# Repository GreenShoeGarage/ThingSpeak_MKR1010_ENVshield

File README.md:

View this project on [CADLAB.io](https://cadlab.io/project/23807). 

# Workspace Health Monitoring Gadget

[https://greenshoegarage.com/2020/10/learning-from-covid-19/](https://greenshoegarage.com/2020/10/learning-from-covid-19/)

## Goal

An open-source device that can monitor 8+ key environmental factors that affect people's perception of a healthy and productive workspace:

* Temperature
* Pressure
* eCO2
* Humidity
* Brightness
* Noise
* TVOC
* PM 2.5um

### Code and hardware is a prototype, no guarentee of any sort is implied. Use at your own risk.

## Functionality

1. Monitor 8 environmental factors
   1. Central processing of all sensor data
2. Record the telemetry locally
   1. 24-hour rolling log
   2. Store on microSD card
3. Display the telemetry locally
   1. Display new data point every 3 seconds
4. Transmit telemetry to web-based cloud service
   1. Send latest sensor readings every 10 minutes

## Bill of Materials

| Supplier | Product ID | Quantity | Description | Unit Price | Function | 
| :--- | :--- | :--- | :--- | :--- | :--- |  
| Mouser | 782-ABX00023 | 1 | MKR1010 | $32.10 | Processing and Comms | 
| Mouser | 782-ASX00011 | 1 | MKR ENV Shield | $34.40 | Temp, UVA/UVB/UV Index, Humidity, Pressure, Lux |
| Adafruit | 3709 | 1 | SGP30 Air Quality Sensor Breakout | $19.95 | VOC, eCO2 | 
| Adafruit | 4632 | 1 | PMSA003I Air Quality Breakout | $44.95 | Particulate Matter | 
| Adafruit | 421 | 1 | I2S MEMS Microphone Breakout SPH0645LM4H | $6.95 | Noise | 

Get the PCB from OSHPark: [https://oshpark.com/shared\_projects/NU4I8Xzd](https://oshpark.com/shared_projects/NU4I8Xzd)

PartsBox Project BOM: [https://partsbox.com/mbparks/project/1s51nh9teghyx9e4by3gwn3nxp/](https://partsbox.com/mbparks/project/1s51nh9teghyx9e4by3gwn3nxp/)

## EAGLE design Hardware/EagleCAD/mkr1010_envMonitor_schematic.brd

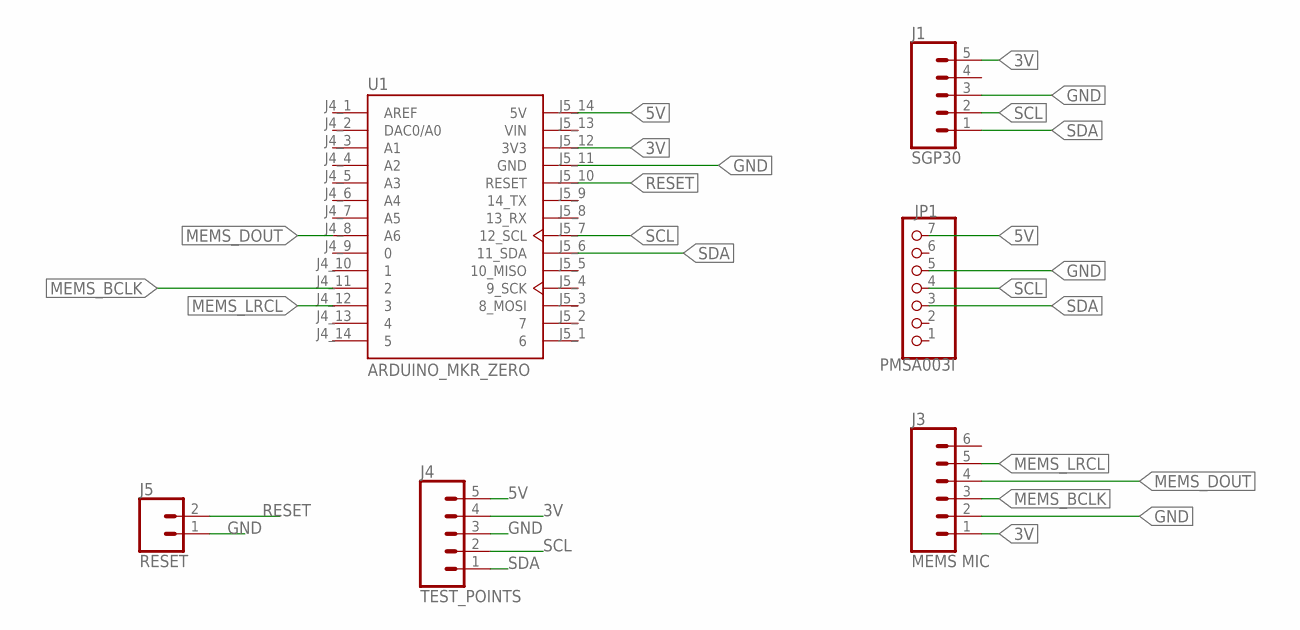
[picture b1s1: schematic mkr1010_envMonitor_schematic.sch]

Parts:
J1: SGP30; 1X05
J3: MEMS MIC; 1X06
J4: TEST_POINTS; 1X05
J5: RESET; 1X02
JP1: PMSA003I; 1X07
U1: ARDUINO_MKR_ZERO; MODULE_ARDUINO_MKR_ZERO

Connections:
3V: J1.5, J3.1, J4.4, U1.J5_12 (3V3)
5V: J4.5, JP1.7, U1.J5_14 (5V)
GND: J1.3, J3.2, J4.3, J5.1, JP1.5, U1.J5_11 (GND)
MEMS_BCLK: J3.3, U1.J4_11 (2)
MEMS_DOUT: J3.4, U1.J4_8 (A6)
MEMS_LRCL: J3.5, U1.J4_12 (3)
RESET: J5.2, U1.J5_10 (RESET)
SCL: J1.2, J4.2, JP1.4, U1.J5_7 (12_SCL)
SDA: J1.1, J4.1, JP1.3, U1.J5_6 (11_SDA)
VIN: U1.J5_13 (VIN)

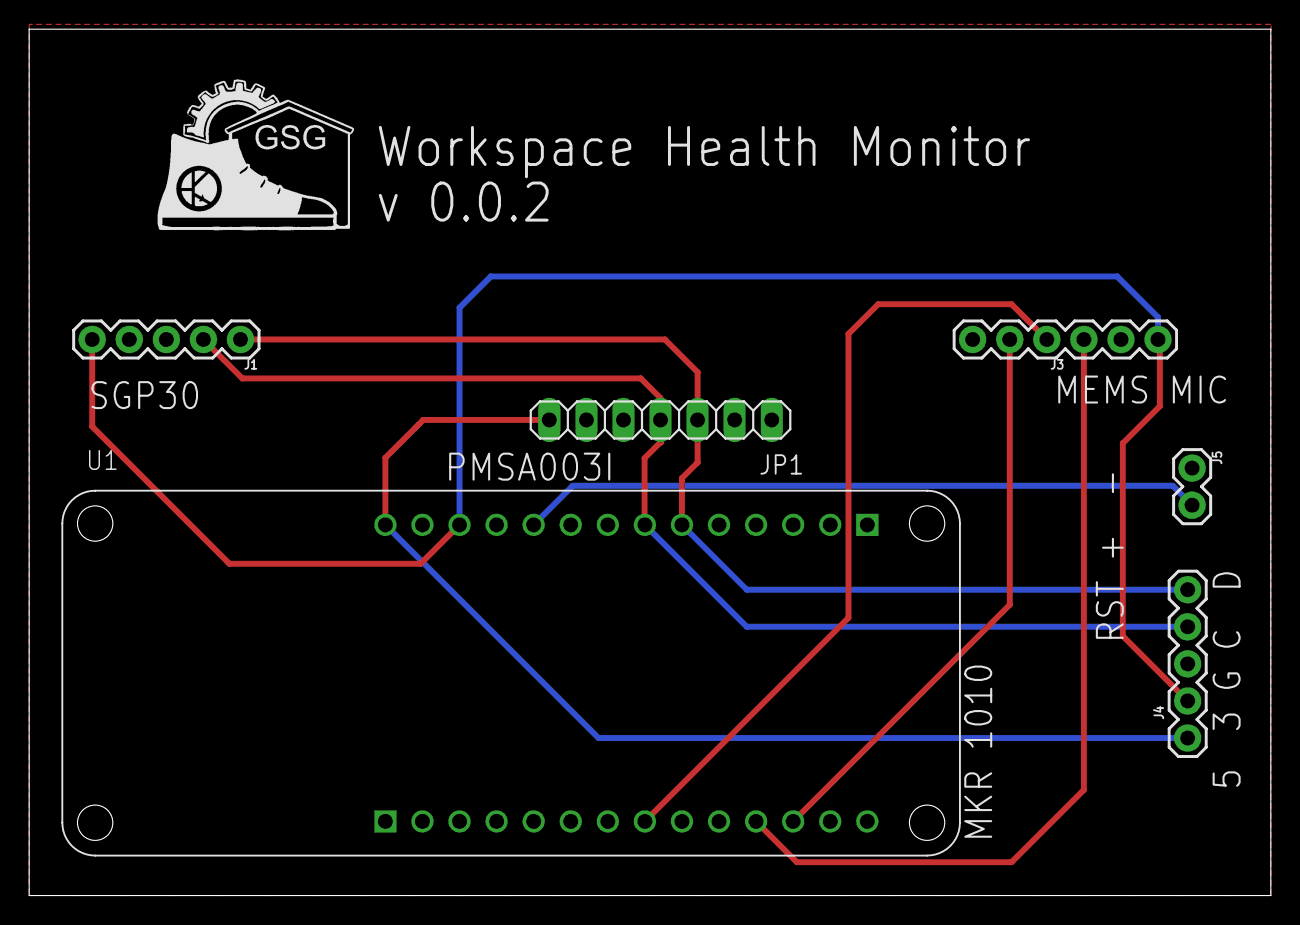
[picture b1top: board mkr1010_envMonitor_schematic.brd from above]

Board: 2 copper layers, 85.1 x 59.4 mm, 6 parts (0 on the bottom side), 9 nets.

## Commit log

2020-06-21 init commit
2020-06-28 added I2S microphone to analyze sound noise
2020-06-28 cleaned up variable names
2020-06-28 update debug messages
2020-07-21 added Adafruit PMSA003I Air Quality Breakout
    PMSA003I Air Quality Breakout (PM0.3-100um)
2020-07-21 remove unnecessary files
2020-07-21 Corrected for MKR1010 LEDs
2020-07-29 added support for SGP30 sensor (eCO2 and TVOC)
2020-10-05 test
2020-10-05 test2
2020-10-11 init hardware (board/schematic) commit
2020-10-11 init Documentation commit
2020-10-12 Added ThingSpeak graph images
2020-10-25 GitBook: [master] 2 pages modified
2020-11-02 Corrected PMSA003I board layout (6pin vs 7pin header)
2020-11-02 PCB images
2020-11-02 Thicker walls for enclosure
2020-11-22 code cleanup, no functional changes
2020-11-22 tweak setup()
2020-11-22 updated doc with v0.0.2 PCB
2020-11-22 new CAM files for PCB v0.0.2
2020-11-22 renamed firmware .ino file
2020-12-08 GitBook: [master] one page modified
2020-12-08 GitBook: [master] 2 pages and one asset modified
2021-01-28 Backlink to CADLAB.io has been added.
2021-02-24 Sending TVOC reading instead of UVIndex (ThingSpeak Field #5)

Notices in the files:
parts and their libraries:
SparkFun-Connectors: Licensing: Creative Commons ShareAlike 4.0 International - https://creativecommons.org/licenses/by-sa/4.0
